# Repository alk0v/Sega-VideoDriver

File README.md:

# Sega-VideoDriver
Schematic and PCB for VHS-based game Sega Video Driver

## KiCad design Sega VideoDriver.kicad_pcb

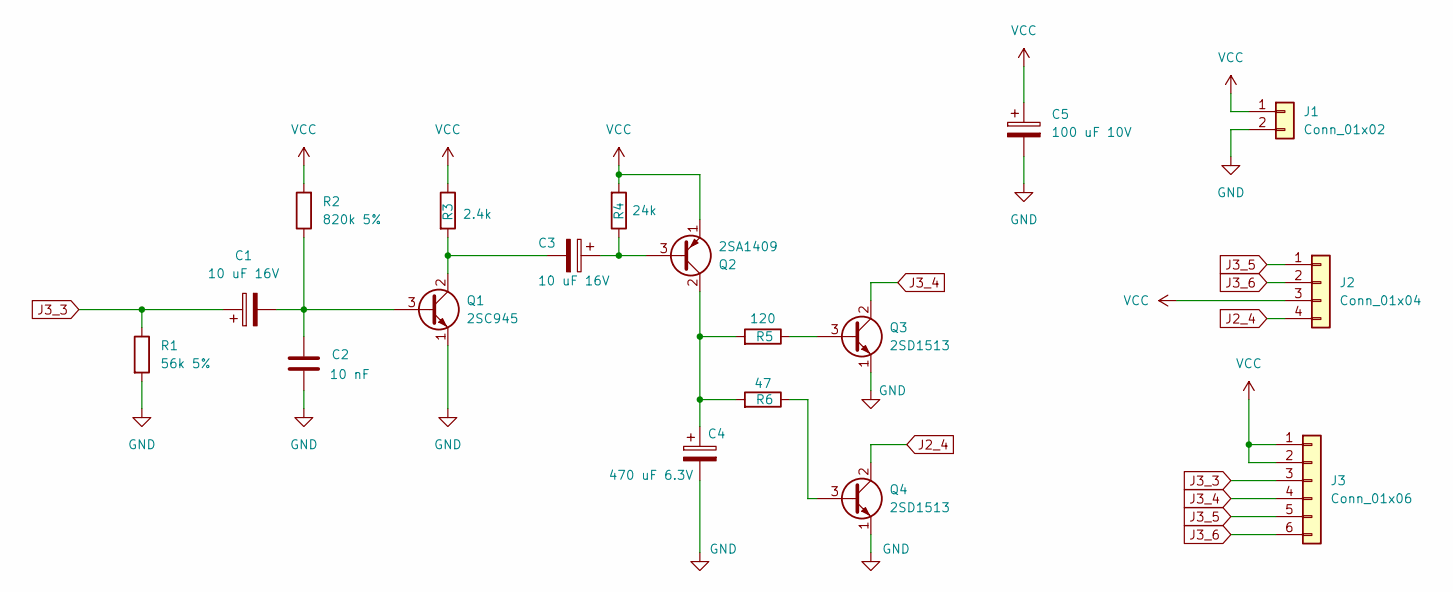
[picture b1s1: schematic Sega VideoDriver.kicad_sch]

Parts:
C1, C3: 10 uF 16V; CP_Radial_D8.0mm_P5.00mm
C2: 10 nF; C_Disc_D5.0mm_W2.5mm_P5.00mm
C4: 470 uF 6.3V; CP_Radial_D8.0mm_P5.00mm
C5: 100 uF 10V; CP_Radial_D8.0mm_P5.00mm
J1: Conn_01x02; row_2pin_5mm
J2: Conn_01x04; row_4pin_5mm
J3: Conn_01x06; row_6pin_combined
Q1: 2SC945; TO-92_Inline_Wide
Q2: 2SA1409; TO-92_Inline_Wide
Q3, Q4: 2SD1513; TO-92_Inline_Wide
R1: 56k 5%; R_Axial_DIN0207_L6.3mm_D2.5mm_P10.16mm_Horizontal
R2: 820k 5%; R_Axial_DIN0207_L6.3mm_D2.5mm_P10.16mm_Horizontal
R3: 2.4k; R_Axial_DIN0207_L6.3mm_D2.5mm_P10.16mm_Horizontal
R4: 24k; R_Axial_DIN0207_L6.3mm_D2.5mm_P10.16mm_Horizontal
R5: 120; R_Axial_DIN0207_L6.3mm_D2.5mm_P10.16mm_Horizontal
R6: 47; R_Axial_DIN0207_L6.3mm_D2.5mm_P10.16mm_Horizontal

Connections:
GND: C2.1, C4.2, C5.2, J1.2, Q1.1 (E), Q3.1 (E), Q4.1 (E), R1.2
J2_4: J2.4, Q4.2 (C)
J3_3: C1.1, J3.3, R1.1
J3_4: J3.4, Q3.2 (C)
J3_5: J2.1, J3.5
J3_6: J2.2, J3.6
unnamed: C1.2, C2.2, Q1.3 (B), R2.1
unnamed: C3.2, Q1.2 (C), R3.2
unnamed: C3.1, Q2.3 (B), R4.1
unnamed: C4.1, Q2.2 (C), R5.2, R6.2
unnamed: Q3.3 (B), R5.1
unnamed: Q4.3 (B), R6.1
VCC: C5.1, J1.1, J2.3, J3.1, J3.2, Q2.1 (E), R2.2, R3.1, R4.2

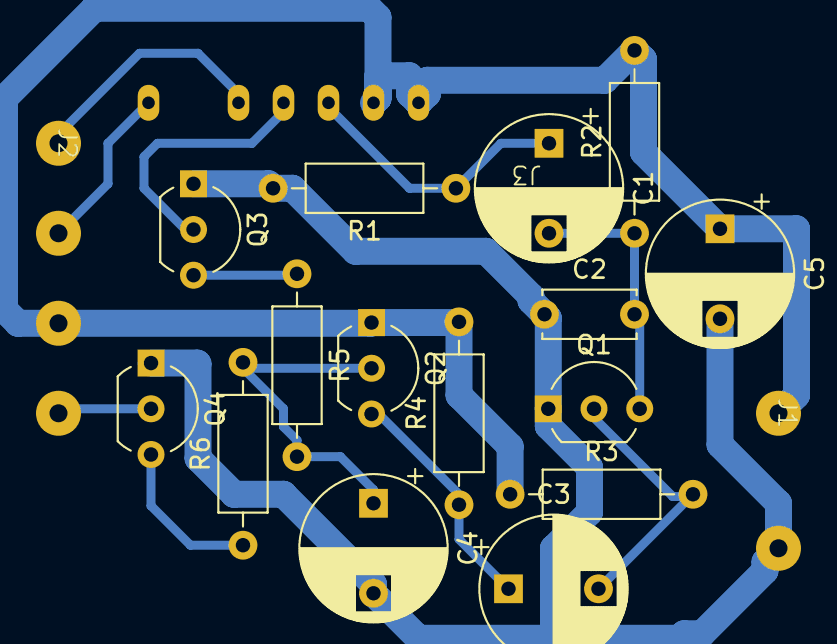
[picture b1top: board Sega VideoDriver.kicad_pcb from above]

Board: 2 copper layers, 18 parts (0 on the bottom side), 13 nets.

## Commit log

2025-08-23 Init commit
